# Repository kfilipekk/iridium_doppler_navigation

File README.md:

# NAVCORE-SoOP

A 46.5 × 47.2 mm, 6-layer STM32H743 flight controller that navigates without GPS using the Doppler shift of Iridium satellites. It runs ArduPilot with a MatekH743-compatible pinout. Made by Krystian Filipek for my GNSS-denied drone.

<div align="center">

</div>

## Results

### Castle Mound, Cambridge (16 Nov 2026)
First session under the real sky: the board on a tripod with the HC610 antenna, GPS denied in software for 30 and 52 minutes. In 1 h 42 min it heard 17,106 bursts and fused 11,383. Each S-curve is a satellite passing over: dots are measured bursts, lines are the Doppler predicted from its orbit.

Started 3 km off with no GPS and left at rest, Iridium alone settles to 50-130 m median error in replay.

### Two flights (18-19 Nov 2026)
On Stansted → Bremen and Hamburg → Gatwick the board was in my hand luggage at the window, logging the radio, IMU and cabin pressure, with a u-blox GPS logged as truth. I replayed the logs afterwards with GPS cut at wheels-off: the IMU corrected by Iridium Doppler, and the cabin barometer for height.

| Median error over 8 filter settings | Cruise (15-45 min) | Descent (45-75 min) |
|---|---|---|
| FR3634 Stansted → Bremen | 2.8-3.0 km | 3.7-6.0 km |
| EZY8636 Hamburg → Gatwick | 3.5-3.9 km | 3.2-3.4 km |
| The same IMU without Iridium | over 1,000 km | |

None of the 16 runs diverged. The orbits are Space-Track elements from before take-off.

<div align="center">

</div>

These are replays of the logs. In the air the I/Q was mirrored (see Known Issues), so nothing decoded live. The firmware fixes that now; a live run is next.

## Features

### Iridium Navigation
Optical flow and visual-inertial odometry drift without bound over long flights. Iridium NEXT satellites orbit at ~780 km and ~7.5 km/s, and their Ring Alert bursts at 1626.27 MHz arrive shifted by up to ±36 kHz. The shift depends on where you are, so enough bursts give a position, and unlike the IMU it doesn't drift.

- **L-band Receiver** - MAX2112 direct-conversion tuner and OPA2374 baseband filter into the ADCs
- **Antenna Feed** - MMCX port with a current-limited 5 V feed for the active antenna, reported as open, ok or short
- **On-board Navigation** - burst detection, SGP4 orbits and the position solve run on the H743 and feed ArduPilot's EKF as a GPS
- **Spoofing Check** - the real GPS is checked against the Iridium-only fix before it is trusted

### Hardware
| Subsystem | Components |
|-----------|------------|
| MCU | STM32H743VIT6, Cortex-M7 @ 480 MHz, 2 MB flash, 1 MB RAM |
| IMUs | ICM-45686 (SPI1) and ICM-42605 (SPI4) on a separate analogue 3.3 V rail, shared with the tuner |
| Barometer | MS5611 on I2C2 |
| Storage | W25Q128 flash for the orbit catalogue, microSD over SDIO |
| Power | 3S-5S input with TVS and reverse-polarity protection, two LMR33630 bucks (1.6 A system, 2.1 A payload) and three 3.3 V LDOs |
| Connectors | Latching JST-GH on every cable port, two servo headers, MMCX, USB-C, TC2030 SWD pads |
| Protection | ESD clamp on every cable-facing signal, series resistors on the motor, telemetry, current, lidar and servo lines |

### Layer Stackup
```
F.Cu:   MCU, RF receiver, bucks and LDOs, flash, the edge connectors
In1.Cu: Continuous ground plane
In2.Cu: Mixed signal with GND fill
In3.Cu: Mixed signal with GND fill
In4.Cu: Split power planes (+5V, +5V_PAYLOAD, +3V3, VBAT)
B.Cu:   IMUs, baro, both crystals, CAN, microSD, the underside connectors
```

### On the Drone
30.5 mm stack mount, DShot ESC on `J2`, optical flow on `J14`, lidar on `J11`, companion computer on `J21`, DroneCAN on `J6`

### How It Compares
| | NAVCORE-SoOP | SpeedyBee F405 V4 | Matek H743-SLIM V3 | Pixhawk 6C |
|---|---|---|---|---|
| MCU | STM32H743 | STM32F405 | STM32H743 | STM32H743 + F103 |
| IMUs | ICM-45686 + ICM-42605 | ICM-42688-P | ICM-42688-P + ICM-42605 | ICM-42688-P + BMI088 |
| Input | 3-5S | 3-6S | 2-8S | power module |
| Port ESD | every cable signal | none stated | none stated | none stated |
| Position without GNSS | Iridium Doppler | none | none | none |

It has no OSD and no 9-12 V video rail, and it takes 5S at most.

## Known Issues (Rev E)

- **I/Q mirrored.** The I and Q channels arrive swapped, so the receiver heard every burst's mirror image, about 25 dB down. The firmware now turns the spectrum the right way up from Ring Alert decodes (`swap_iq` in `soop.cfg` forces it).
- **RF line impedance.** The board was ordered on JLCPCB's default stackup, which puts the antenna line near 67 Ω rather than 50 Ω.
- **No PPS line.** ArduPilot stamps u-blox fixes when the message arrives, so `gps_lag_s` corrects the time tag. An optional PPS input on TP3 is wired in firmware but untested.
- **Channel 4 unused.** The channel at 1626.4375 MHz carries about 55% more bursts but sits outside the DSP's ±62.5 kHz window; using it live needs a second window.

## Getting Started

### Prerequisites
- **KiCad 9** to open the board and schematic
- **Python 3** with numpy and sgp4, and **ngspice** for the circuit simulations
- **ArduPilot toolchain** for the firmware (`tools/build_firmware.sh` pins Copter-4.7.0)

### Building
1. Clone the repository:
   ```bash
   git clone https://github.com/kfilipekk/iridium_drone.git
   cd iridium_drone
   ```

2. Simulate the analogue blocks (bucks, LDOs, antenna feed, tuner PLL, baseband filter):
   ```bash
   python3 sim/run_suite.py
   ```

3. Build the navigation code and its tests for the host (SGP4, burst detection, the position solve):
   ```bash
   make -C firmware/soop
   ```

4. Build ArduPilot for the board with the SoOP backend:
   ```bash
   bash tools/build_firmware.sh
   ```

### Checking the Board
The checks need KiCad's Python (the `pcbnew` module), and `irdrop.py` needs numpy. Run them from the repository root:
```bash
kicad-cli pcb drc --schematic-parity NAVCORE-SoOP.kicad_pcb
python3 tools/check.py geometry     # acute corners, dangling ends, dead copper, vias in pads
python3 tools/check.py backside     # pins landing under parts on the other side
python3 tools/check.py footprints   # pad counts against JLCPCB's own parts
python3 tools/irdrop.py check       # DC drop and current density on every power rail
python3 tools/fab.py bundle         # gerbers, BOM, CPL and the order sheet, into fab/
```
`--help` on any of them lists the rest.

### Field Sessions and Replays
```bash
python3 tools/soop_plan.py 52.212 0.115           # rank the next hours by satellite geometry
python3 tools/soop_session.py OUT.csv off:1800,on:300   # record both receivers, deny GPS on a plan
python3 tools/soop_live.py OUT.csv                # watch it in the browser
python3 tools/soop_replay.py LOG.BIN TLE --static # run a log through the navigation again
python3 tools/soop_extract.py LOG.BIN LOG.npz     # a flight log to numpy
python3 tools/soop_ins.py LOG.npz TLE BURSTS.csv TRUTH.npz --out FIXES.csv
python3 tools/soop_flightmap.py --flight "LABEL|LOG.npz|FIXES.csv" --basemap DIR map.html
```

### Ordering
The JLCPCB files are in `fab/`: the Gerber and drill bundle, BOM, pick-and-place and schematic PDF. Order 6 layers, 1 oz copper inside and out, ENIG, epoxy-filled and capped vias, and assembly on both sides. Name a controlled-impedance stackup if you want the antenna line at 50 Ω.

## Repository Structure

```
├── NAVCORE-SoOP.kicad_pcb   # PCB
├── NAVCORE-SoOP.kicad_sch   # Schematic, generated from tools/design.py
├── fab/                     # JLCPCB order files
├── firmware/                # ArduPilot hwdef, the SoOP backend and the on-board navigation
├── tools/                   # Design model, board checks, and the soop_* field and replay tools
├── sim/                     # ngspice simulations of the analogue blocks
├── sitl/tle/                # Iridium orbital elements for the host tools
├── cad/                     # OpenSCAD airframe, printed mounts and renders
└── libraries/               # Footprint and symbol libraries
```

## Next

- A live run on the current firmware at Castle Mound
- A second DSP window so channel 4 is used live
- Per-satellite transmitter offsets and fresher orbits, which set the static floor more than the DSP does
- A downward radar for velocity, then flying it on the drone
- Writing up the airliner results

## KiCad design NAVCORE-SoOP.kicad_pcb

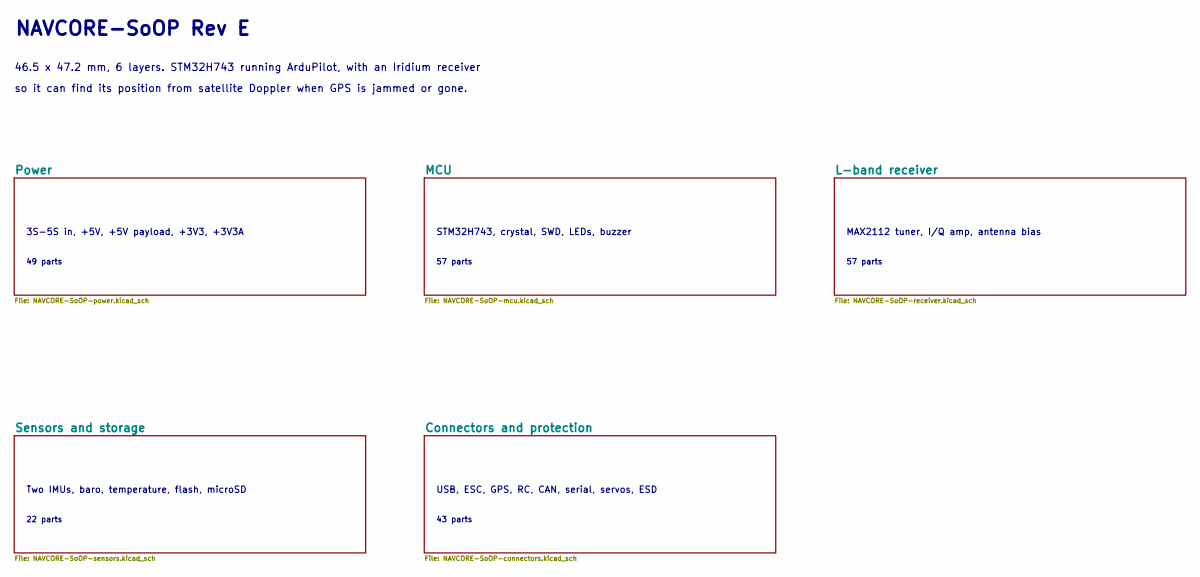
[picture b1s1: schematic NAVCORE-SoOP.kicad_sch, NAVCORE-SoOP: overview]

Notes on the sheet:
NAVCORE-SoOP Rev E
46.5 x 47.2 mm, 6 layers. STM32H743 running ArduPilot, with an Iridium receiver
so it can find its position from satellite Doppler when GPS is jammed or gone.
3S-5S in, +5V, +5V payload, +3V3, +3V3A
49 parts
STM32H743, crystal, SWD, LEDs, buzzer
57 parts
MAX2112 tuner, I/Q amp, antenna bias
Two IMUs, baro, temperature, flash, microSD
22 parts
USB, ESC, GPS, RC, CAN, serial, servos, ESD
43 parts

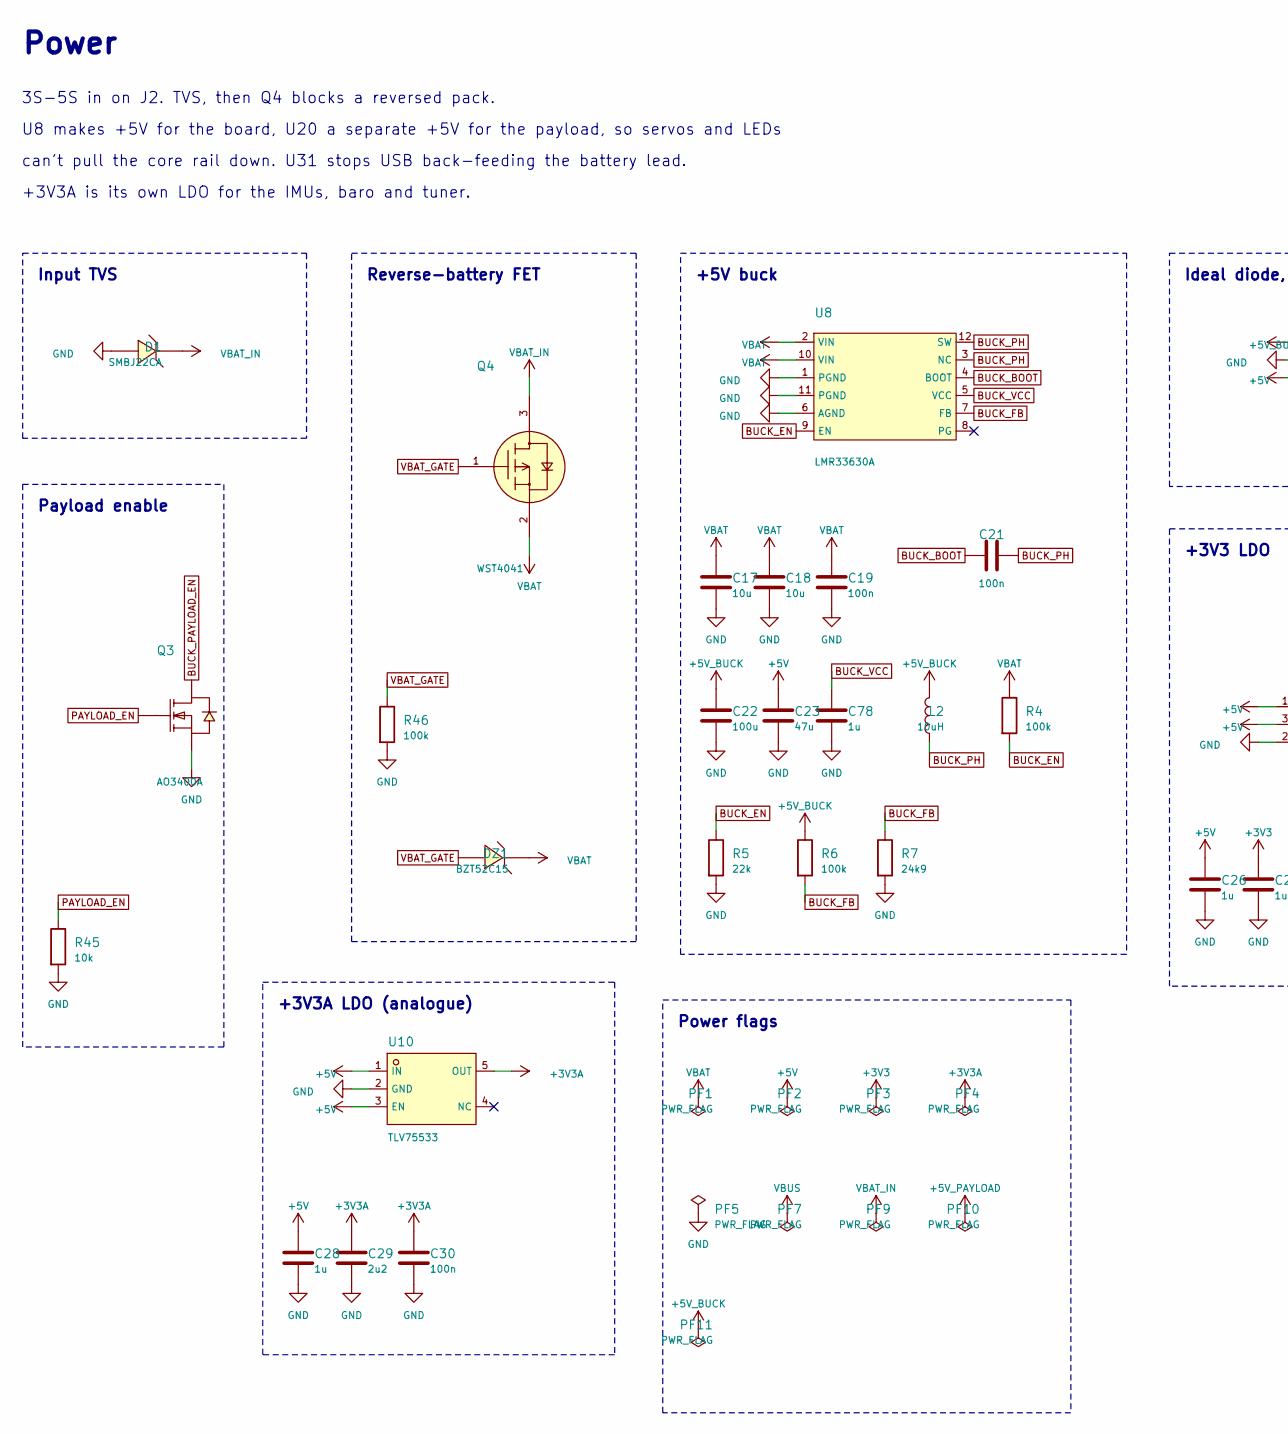
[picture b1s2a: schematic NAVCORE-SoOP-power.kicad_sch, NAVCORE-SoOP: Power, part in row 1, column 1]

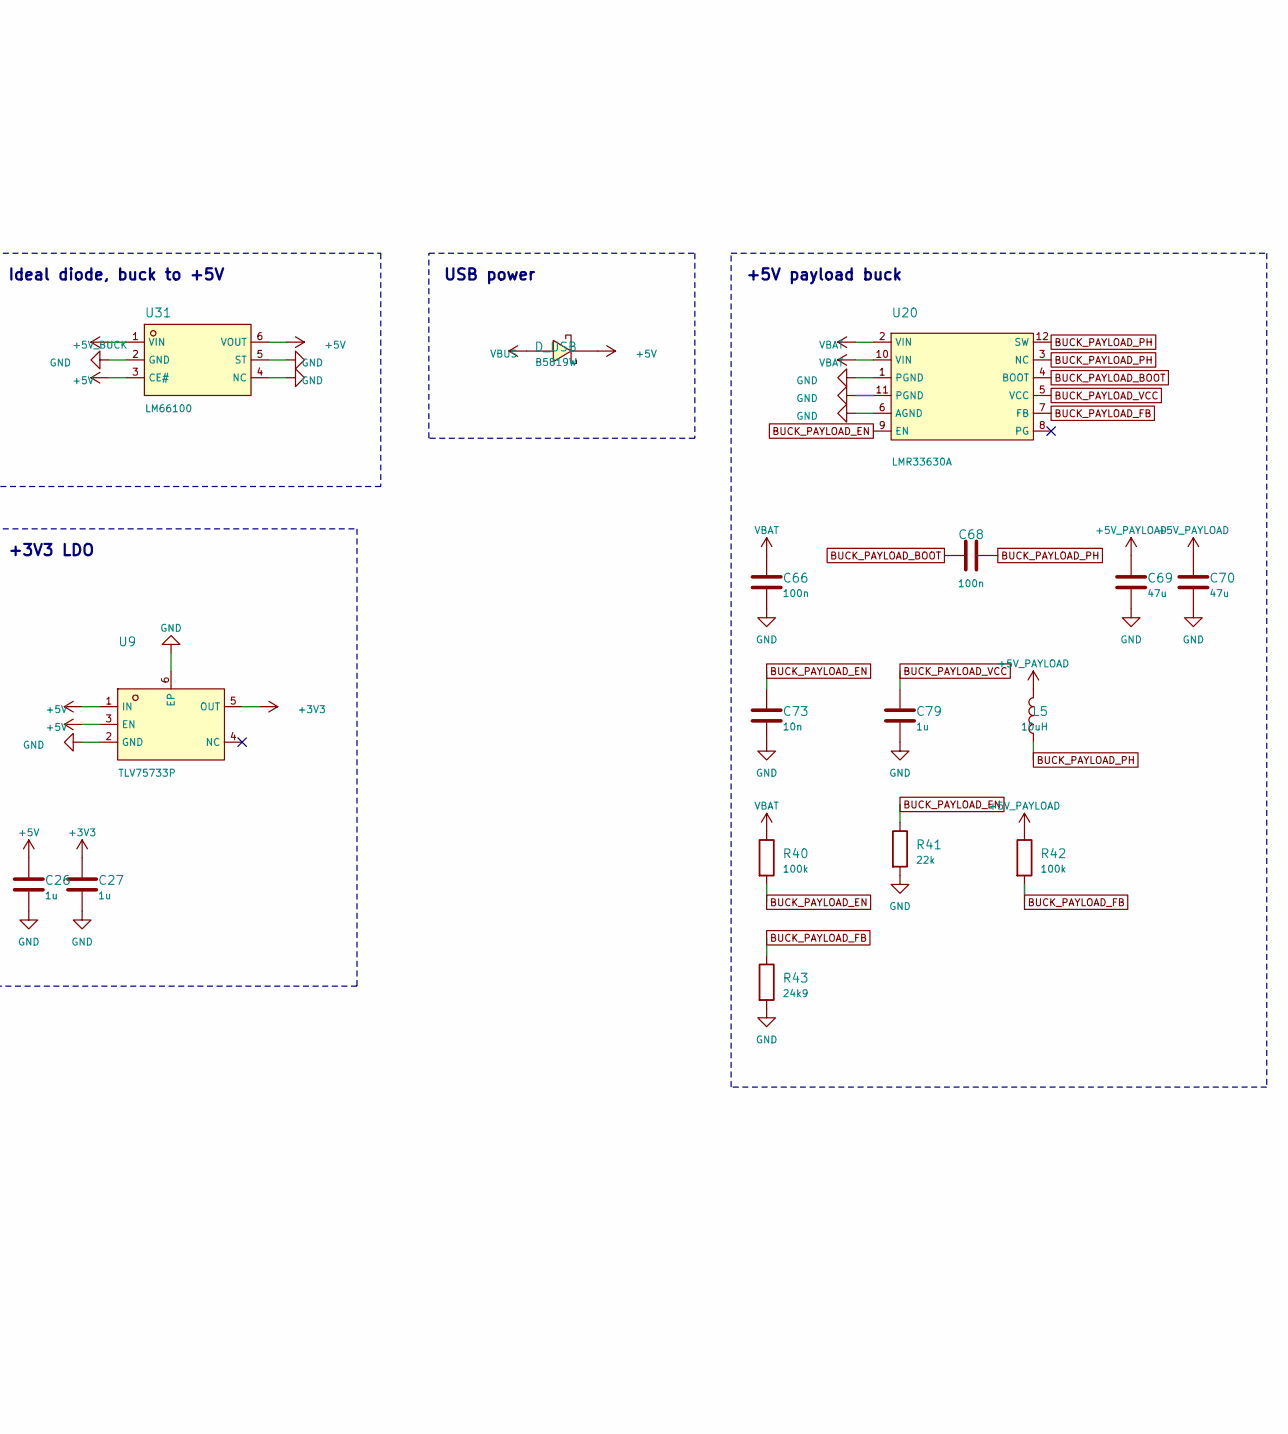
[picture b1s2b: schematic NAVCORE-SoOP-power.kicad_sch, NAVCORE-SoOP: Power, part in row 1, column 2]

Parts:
C17, C18: 10u; C_1206_3216Metric; LCSC C13585
C19, C66: 100n; C_0402_1005Metric; LCSC C307331
C21, C30, C68: 100n; C_0402_1005Metric; LCSC C1525
C22: 100u; C_1206_3216Metric; LCSC C883598
C23, C69, C70: 47u; C_1206_3216Metric; LCSC C96123
C26, C27, C28, C78, C79: 1u; C_0402_1005Metric; LCSC C52923
C29: 2u2; C_0402_1005Metric; LCSC C12530
C73: 10n; C_0402_1005Metric; LCSC C15195
D1: SMBJ22CA; SMB_L4.6-W3.6-LS5.3-RD; LCSC C113994
DZ1: BZT52C15; SOD-123_L2.7-W1.6-LS3.7-RD; LCSC C173427
D_USB: B5819W; SOD-123_L2.7-W1.6-LS3.7-RD-1; LCSC C8598
L2: 10uH; L_APV_ANR4030; LCSC C167879
L5: 10uH; L_APV_ANR5040; LCSC C354610
PF1, PF2, PF3, PF4, PF5, PF7, PF9, PF10, PF11: PWR_FLAG
Q3: AO3400A; SOT-23-3_L2.9-W1.3-P1.90-LS2.4-BR; LCSC C20917
Q4: WST4041; SOT-23-3_L2.9-W1.3-P1.90-LS2.4-BR; LCSC C148357
R4, R6, R40, R42, R46: 100k; R_0402_1005Metric; LCSC C25741
R5, R41: 22k; R_0402_1005Metric; LCSC C25768
R7, R43: 24k9; R_0402_1005Metric; LCSC C25874
R45: 10k; R_0402_1005Metric; LCSC C25744
U8, U20: LMR33630A; VQFN-12_L3.0-W2.0-P0.65-BL_TI_RNX; LCSC C2861505
U9: TLV75733P; SOT-23-5_L2.9-W1.6-P0.95-LS2.8-BL-EP; LCSC C22399950
U10: TLV75533; SOT-23-5_L3.0-W1.7-P0.95-LS2.8-BR; LCSC C404027
U31: LM66100; SC-70-6_L2.0-W1.3-P0.65-LS2.1-BL; LCSC C2869734

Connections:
+3V3: C27.1, PF3.1, U9.5 (OUT); also elsewhere on the board
+3V3A: C29.1, C30.1, PF4.1, U10.5 (OUT); also elsewhere on the board
+5V: C23.1, C26.1, C28.1, D_USB.1 (-), PF2.1, U9.1 (IN), U9.3 (EN), U10.1 (IN), U10.3 (EN), U31.3 (CE#), U31.6 (VOUT); also elsewhere on the board
+5V_BUCK: C22.1, L2.2, PF11.1, R6.1, U31.1 (VIN)
+5V_PAYLOAD: C69.1, C70.1, L5.2, PF10.1, R42.1; also elsewhere on the board
BUCK_BOOT: C21.1, U8.4 (BOOT)
BUCK_EN: R4.2, R5.1, U8.9 (EN)
BUCK_FB: R6.2, R7.1, U8.7 (FB)
BUCK_PAYLOAD_BOOT: C68.1, U20.4 (BOOT)
BUCK_PAYLOAD_EN: C73.1, Q3.3 (D), R40.2, R41.1, U20.9 (EN)
BUCK_PAYLOAD_FB: R42.2, R43.1, U20.7 (FB)
BUCK_PAYLOAD_PH: C68.2, L5.1, U20.3 (NC), U20.12 (SW)
BUCK_PAYLOAD_VCC: C79.1, U20.5 (VCC)
BUCK_PH: C21.2, L2.1, U8.3 (NC), U8.12 (SW)
BUCK_VCC: C78.1, U8.5 (VCC)
GND: C17.2, C18.2, C19.2, C22.2, C23.2, C26.2, C27.2, C28.2, C29.2, C30.2, C66.2, C69.2, C70.2, C73.2, C78.2, C79.2, D1.2 (A2), PF5.1, Q3.2 (S), R5.2, R7.2, R41.2, R43.2, R45.2, R46.2, U8.1 (PGND), U8.6 (AGND), U8.11 (PGND), U9.2 (GND), U9.6 (EP), U10.2 (GND), U20.1 (PGND), U20.6 (AGND), U20.11 (PGND), U31.2 (GND), U31.4 (NC), U31.5 (ST); also elsewhere on the board
PAYLOAD_EN: Q3.1 (G), R45.1; also elsewhere on the board
VBAT: C17.1, C18.1, C19.1, C66.1, DZ1.1 (K), PF1.1, Q4.2 (S), R4.1, R40.1, U8.2 (VIN), U8.10 (VIN), U20.2 (VIN), U20.10 (VIN); also elsewhere on the board
VBAT_GATE: DZ1.2 (A), Q4.1 (G), R46.1
VBAT_IN: D1.1 (A1), PF9.1, Q4.3 (D); also elsewhere on the board
VBUS: D_USB.2 (+), PF7.1; also elsewhere on the board

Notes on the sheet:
Power
3S-5S in on J2. TVS, then Q4 blocks a reversed pack.
U8 makes +5V for the board, U20 a separate +5V for the payload, so servos and LEDs
can't pull the core rail down. U31 stops USB back-feeding the battery lead.
+3V3A is its own LDO for the IMUs, baro and tuner.
Input TVS
Reverse-battery FET
+5V buck
Ideal diode, buck to +5V
USB power
+5V payload buck
Payload enable
+3V3 LDO
+3V3A LDO (analogue)
Power flags

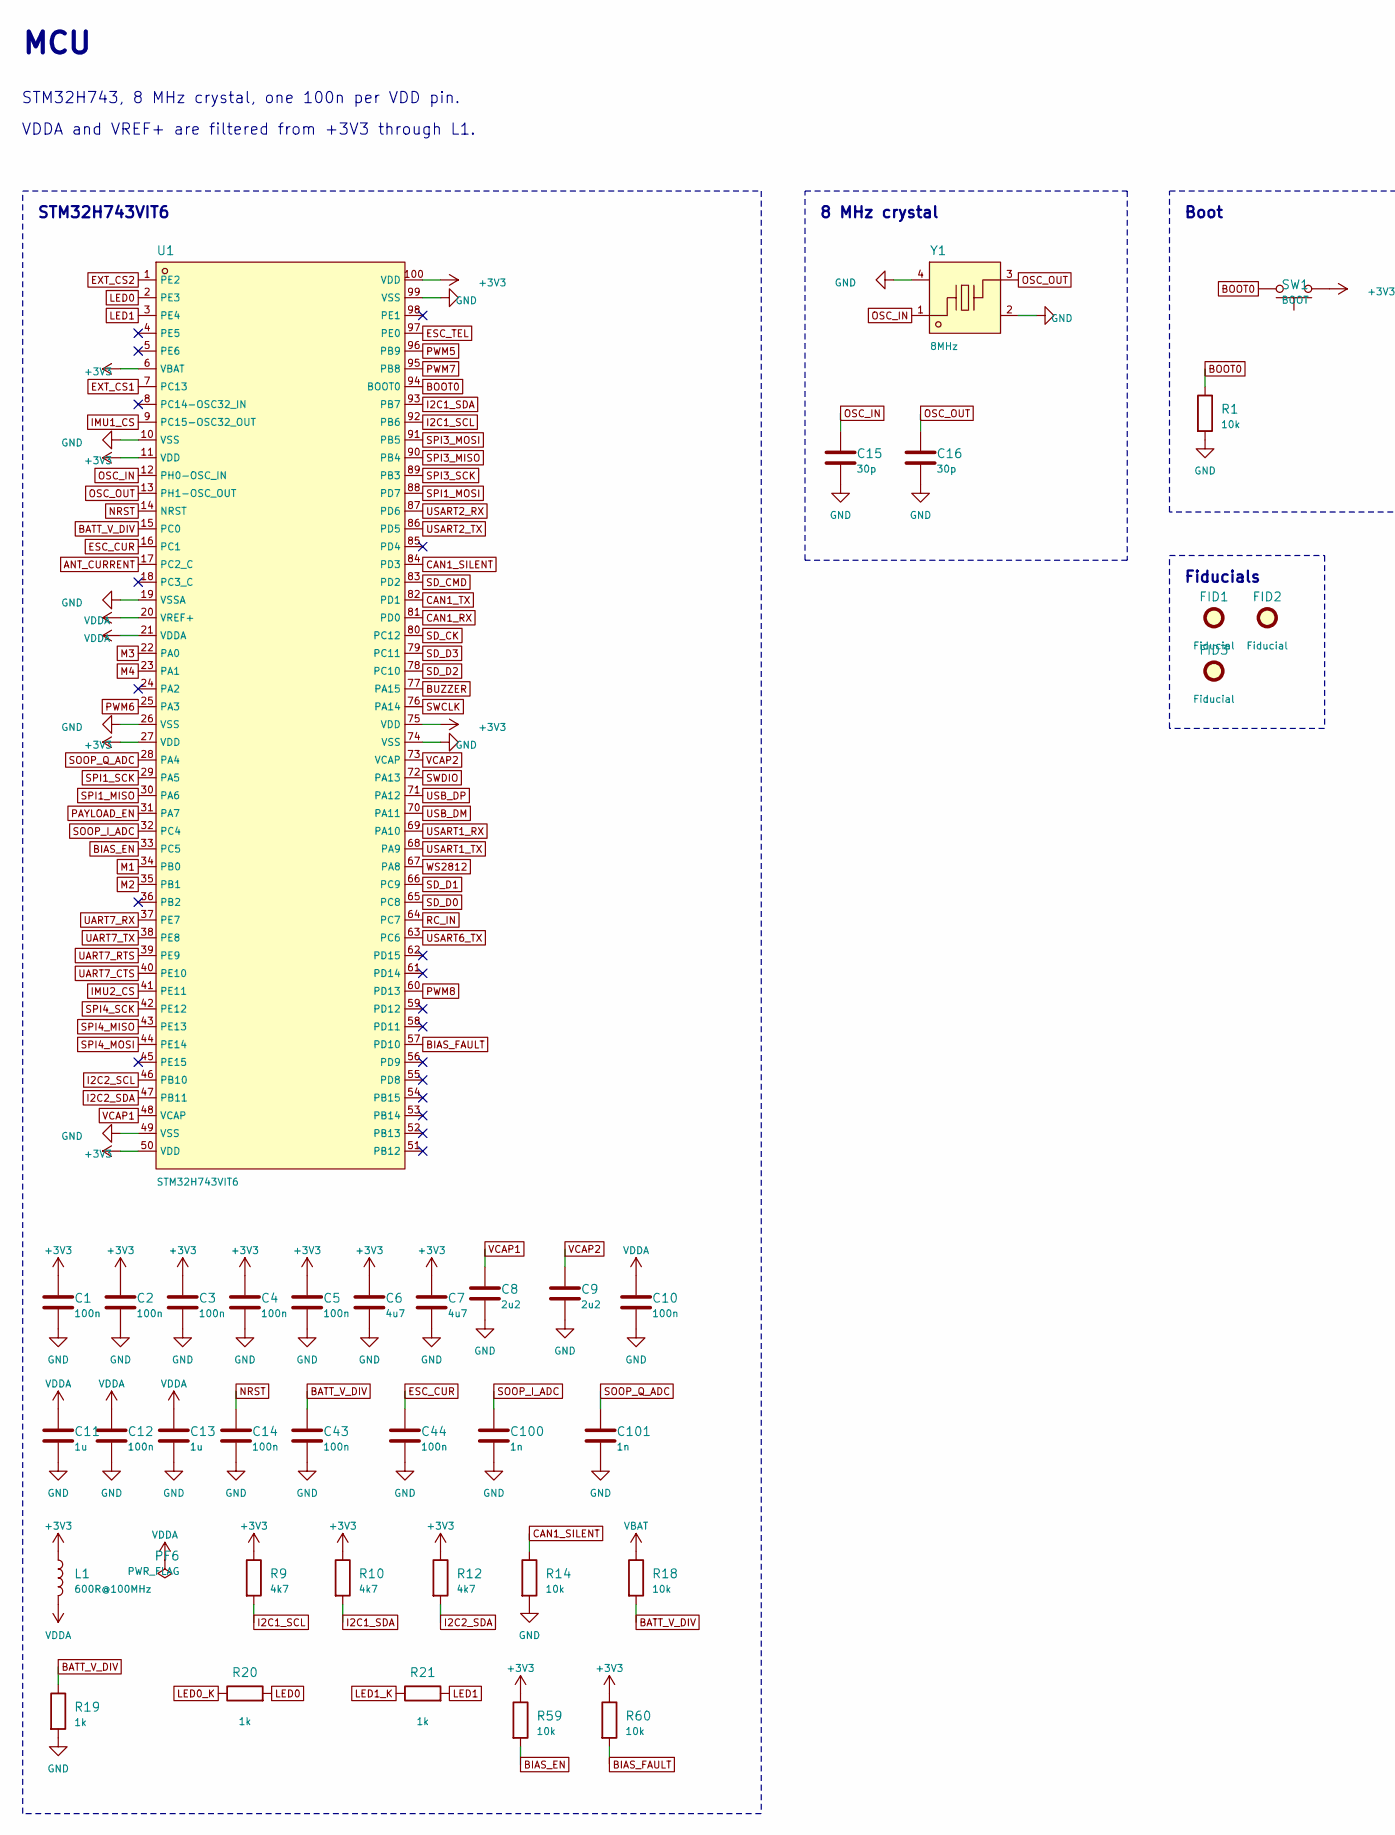
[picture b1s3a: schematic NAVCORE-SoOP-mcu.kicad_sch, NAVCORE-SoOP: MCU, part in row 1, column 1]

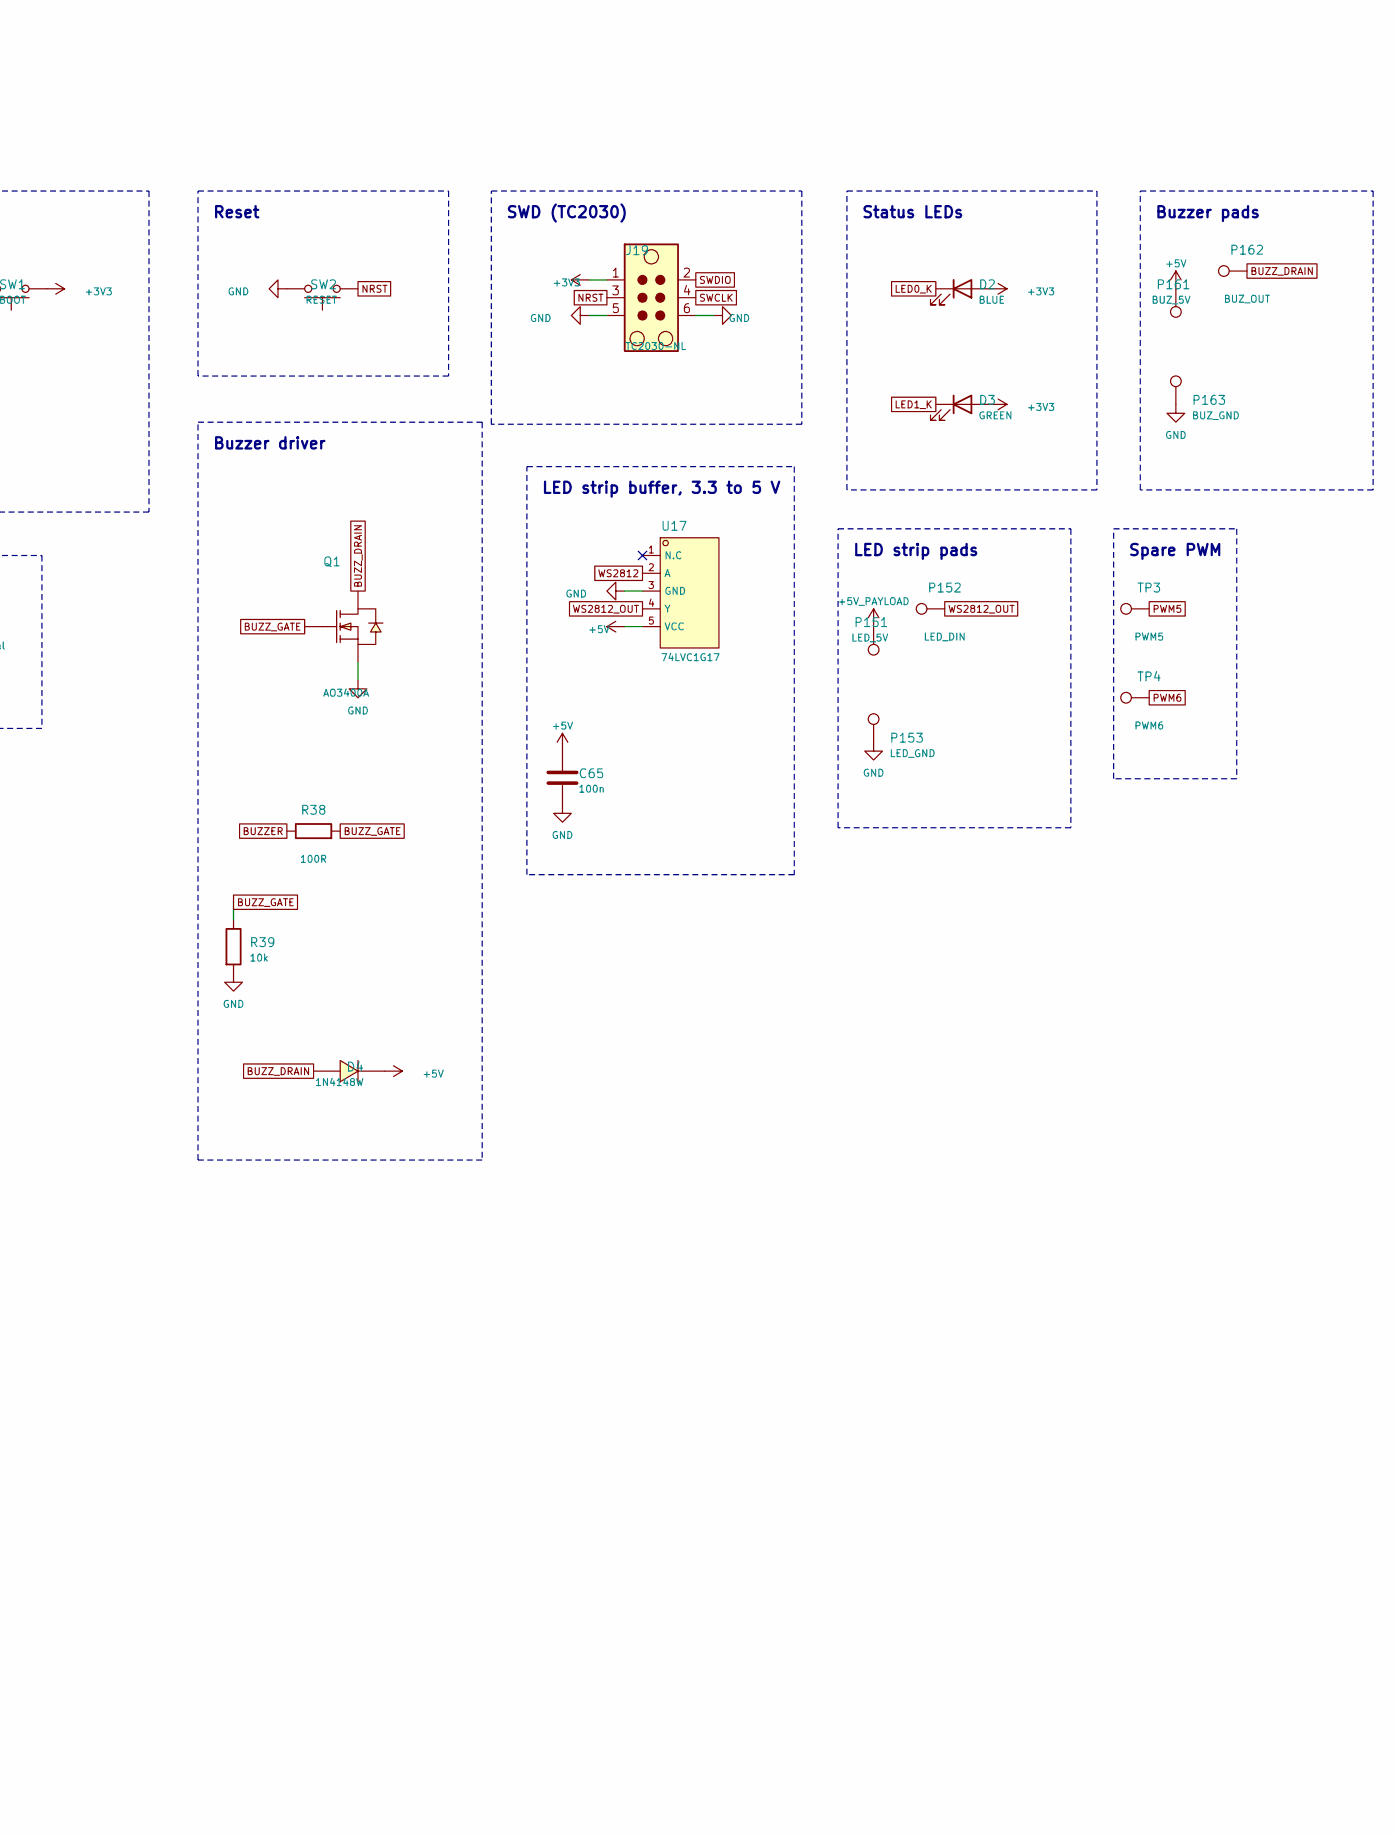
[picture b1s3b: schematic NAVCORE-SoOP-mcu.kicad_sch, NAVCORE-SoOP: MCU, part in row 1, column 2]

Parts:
C1, C2, C3, C4, C5, C10, C12, C14, C43, C44, C65: 100n; C_0402_1005Metric; LCSC C1525
C6, C7: 4u7; C_0805_2012Metric; LCSC C354262
C8, C9: 2u2; C_0402_1005Metric; LCSC C12530
C11, C13: 1u; C_0402_1005Metric; LCSC C52923
C15, C16: 30p; C_0402_1005Metric; LCSC C107004
C100, C101: 1n; C_0201_0603Metric; LCSC C710792
D2: BLUE; LED_0603_1608Metric; LCSC C965807
D3: GREEN; LED_0603_1608Metric; LCSC C965804
D4: 1N4148W; SOD-123F_L2.7-W1.6-LS3.8-RD; LCSC C81598
FID1, FID2, FID3: Fiducial; Fiducial_1mm_Mask2mm
J19: TC2030-NL; Tag-Connect_TC2030-IDC-NL_2x03_P1.27mm_Vertical
L1: 600R@100MHz; L_0805_2012Metric; LCSC C1017
P151: LED_5V; TestPoint_Pad_1.5x1.5mm
P152: LED_DIN; TestPoint_Pad_1.5x1.5mm
P153: LED_GND; TestPoint_Pad_1.5x1.5mm
P161: BUZ_5V; TestPoint_Pad_1.5x1.5mm
P162: BUZ_OUT; TestPoint_Pad_1.5x1.5mm
P163: BUZ_GND; TestPoint_Pad_1.5x1.5mm
PF6: PWR_FLAG
Q1: AO3400A; SOT-23-3_L2.9-W1.3-P1.90-LS2.4-BR; LCSC C20917
R1, R14, R39, R59, R60: 10k; R_0402_1005Metric; LCSC C25744
R9, R10, R12: 4k7; R_0402_1005Metric; LCSC C25900
R18: 10k; R_0603_1608Metric; LCSC C25804
R19, R20, R21: 1k; R_0402_1005Metric; LCSC C11702
R38: 100R; R_0402_1005Metric; LCSC C25076
SW1: BOOT; SW_SPST_B3U-1000P; LCSC C231329
SW2: RESET; SW_SPST_B3U-1000P; LCSC C231329
TP3: PWM5; TestPoint_Pad_1.5x1.5mm
TP4: PWM6; TestPoint_Pad_1.5x1.5mm
U1: STM32H743VIT6; LQFP-100_L14.0-W14.0-P0.50-LS16.0-BL; LCSC C5271084
U17: 74LVC1G17; SOT-23-5_L3.0-W1.7-P0.95-LS2.8-BR; LCSC C7836
Y1: 8MHz; CRYSTAL-SMD_4P-L3.2-W2.5-BL; LCSC C2682774

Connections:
+3V3: C1.1, C2.1, C3.1, C4.1, C5.1, C6.1, C7.1, D2.2 (A), D3.2 (A), J19.1, L1.1, R9.1, R10.1, R12.1, R59.1, R60.1, SW1.1, U1.6 (VBAT), U1.11 (VDD), U1.27 (VDD), U1.50 (VDD), U1.75 (VDD), U1.100 (VDD); also elsewhere on the board
+5V: C65.1, D4.1 (K), P161.1, U17.5 (VCC); also elsewhere on the board
+5V_PAYLOAD: P151.1; also elsewhere on the board
ANT_CURRENT: U1.17 (PC2_C); also elsewhere on the board
BATT_V_DIV: C43.1, R18.2, R19.1, U1.15 (PC0)
BIAS_EN: R59.2, U1.33 (PC5); also elsewhere on the board
BIAS_FAULT: R60.2, U1.57 (PD10); also elsewhere on the board
BOOT0: R1.1, SW1.2, U1.94 (BOOT0)
BUZZER: R38.1, U1.77 (PA15)
BUZZ_DRAIN: D4.2 (A), P162.1, Q1.3 (D)
BUZZ_GATE: Q1.1 (G), R38.2, R39.1
CAN1_RX: U1.81 (PD0); also elsewhere on the board
CAN1_SILENT: R14.1, U1.84 (PD3); also elsewhere on the board
CAN1_TX: U1.82 (PD1); also elsewhere on the board
ESC_CUR: C44.1, U1.16 (PC1); also elsewhere on the board
ESC_TEL: U1.97 (PE0); also elsewhere on the board
EXT_CS1: U1.7 (PC13); also elsewhere on the board
EXT_CS2: U1.1 (PE2); also elsewhere on the board
GND: C1.2, C2.2, C3.2, C4.2, C5.2, C6.2, C7.2, C8.2, C9.2, C10.2, C11.2, C12.2, C13.2, C14.2, C15.2, C16.2, C43.2, C44.2, C65.2, C100.2, C101.2, J19.5, J19.6, P153.1, P163.1, Q1.2 (S), R1.2, R14.2, R19.2, R39.2, SW2.2, U1.10 (VSS), U1.19 (VSSA), U1.26 (VSS), U1.49 (VSS), U1.74 (VSS), U1.99 (VSS), U17.3 (GND), Y1.2 (GND), Y1.4 (GND); also elsewhere on the board
I2C1_SCL: R9.2, U1.92 (PB6); also elsewhere on the board
I2C1_SDA: R10.2, U1.93 (PB7); also elsewhere on the board
I2C2_SCL: U1.46 (PB10); also elsewhere on the board
I2C2_SDA: R12.2, U1.47 (PB11); also elsewhere on the board
IMU1_CS: U1.9 (PC15-OSC32_OUT); also elsewhere on the board
IMU2_CS: U1.41 (PE11); also elsewhere on the board
LED0: R20.2, U1.2 (PE3)
LED0_K: D2.1 (K), R20.1
LED1: R21.2, U1.3 (PE4)
LED1_K: D3.1 (K), R21.1
M1: U1.34 (PB0); also elsewhere on the board
M2: U1.35 (PB1); also elsewhere on the board
M3: U1.22 (PA0); also elsewhere on the board
M4: U1.23 (PA1); also elsewhere on the board
NRST: C14.1, J19.3, SW2.1, U1.14 (NRST)
OSC_IN: C15.1, U1.12 (PH0-OSC_IN), Y1.1
OSC_OUT: C16.1, U1.13 (PH1-OSC_OUT), Y1.3
PAYLOAD_EN: U1.31 (PA7); also elsewhere on the board
PWM5: TP3.1, U1.96 (PB9)
PWM6: TP4.1, U1.25 (PA3)
PWM7: U1.95 (PB8); also elsewhere on the board
PWM8: U1.60 (PD13); also elsewhere on the board
RC_IN: U1.64 (PC7); also elsewhere on the board
SD_CK: U1.80 (PC12); also elsewhere on the board
SD_CMD: U1.83 (PD2); also elsewhere on the board
SD_D0: U1.65 (PC8); also elsewhere on the board
SD_D1: U1.66 (PC9); also elsewhere on the board
SD_D2: U1.78 (PC10); also elsewhere on the board
SD_D3: U1.79 (PC11); also elsewhere on the board
SOOP_I_ADC: C100.1, U1.32 (PC4); also elsewhere on the board
SOOP_Q_ADC: C101.1, U1.28 (PA4); also elsewhere on the board
SPI1_MISO: U1.30 (PA6); also elsewhere on the board
SPI1_MOSI: U1.88 (PD7); also elsewhere on the board
SPI1_SCK: U1.29 (PA5); also elsewhere on the board
SPI3_MISO: U1.90 (PB4); also elsewhere on the board
SPI3_MOSI: U1.91 (PB5); also elsewhere on the board
SPI3_SCK: U1.89 (PB3); also elsewhere on the board
SPI4_MISO: U1.43 (PE13); also elsewhere on the board
SPI4_MOSI: U1.44 (PE14); also elsewhere on the board
SPI4_SCK: U1.42 (PE12); also elsewhere on the board
SWCLK: J19.4, U1.76 (PA14)
SWDIO: J19.2, U1.72 (PA13)
UART7_CTS: U1.40 (PE10); also elsewhere on the board
UART7_RTS: U1.39 (PE9); also elsewhere on the board
UART7_RX: U1.37 (PE7); also elsewhere on the board
UART7_TX: U1.38 (PE8); also elsewhere on the board
USART1_RX: U1.69 (PA10); also elsewhere on the board
USART1_TX: U1.68 (PA9); also elsewhere on the board
USART2_RX: U1.87 (PD6); also elsewhere on the board
USART2_TX: U1.86 (PD5); also elsewhere on the board
USART6_TX: U1.63 (PC6); also elsewhere on the board
USB_DM: U1.70 (PA11); also elsewhere on the board
USB_DP: U1.71 (PA12); also elsewhere on the board
VBAT: R18.1; also elsewhere on the board
VCAP1: C8.1, U1.48 (VCAP)
VCAP2: C9.1, U1.73 (VCAP)
VDDA: C10.1, C11.1, C12.1, C13.1, L1.2, PF6.1, U1.20 (VREF+), U1.21 (VDDA)
WS2812: U1.67 (PA8), U17.2 (A)
WS2812_OUT: P152.1, U17.4 (Y)

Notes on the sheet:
MCU
STM32H743, 8 MHz crystal, one 100n per VDD pin.
VDDA and VREF+ are filtered from +3V3 through L1.
STM32H743VIT6
8 MHz crystal
Boot
Reset
SWD (TC2030)
Status LEDs
Buzzer driver
Buzzer pads
LED strip buffer, 3.3 to 5 V
LED strip pads
Spare PWM
Fiducials

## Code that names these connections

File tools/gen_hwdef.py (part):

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    (r'^define OSD_ENABLED',     "no analogue OSD fitted"),
    (r'^define HAL_OSD_TYPE_DEFAULT', "no analogue OSD fitted"),
    (r'^ROMFS_WILDCARD libraries/AP_OSD', "no analogue OSD fitted"),
    (r'^PA4 BATT2_VOLTAGE_SENS', "single battery; freed for the SoOP I/Q input"),
    (r'^define HAL_BATT2_',      "single battery"),
    (r'^define HAL_DEFAULT_AIRSPEED_PIN', "no airspeed sensor"),
    (r'^define BOARD_RSSI_ANA_PIN', "RSSI arrives over CRSF"),
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    (r'^IMU Invensense SPI:mpu6000',  "MPU6000 not fitted"),
    (r'^SPIDEV icm20602',        "ICM-20602 not fitted"),
    (r'^SPIDEV mpu6000',         "MPU6000 not fitted"),
    (r'^PC7 TIM3_CH2 TIM3 RCININT',
     "RC is CRSF over USART6 (SERIAL7_PROTOCOL 23), so the timer input on the same pin goes, "
     "and TIM3 drives M1/M2 instead (PPM/SBUS-by-timer receivers lose their input)"),
    (r'^PB13 SPI2_SCK',          "SPI2 served only the analogue OSD, which is not fitted"),
    (r'^PB14 SPI2_MISO',         "SPI2 served only the analogue OSD, which is not fitted"),
    (r'^PB15 SPI2_MOSI',         "SPI2 served only the analogue OSD, which is not fitted"),
    (r'^PC13 IMU3_CS',           "no third IMU fitted; PC13 is the flow port's chip select"),
    (r'^PB9 UART4_TX',           "UART4 was never brought out; PB8 now carries servo PWM7"),
    (r'^PB8 UART4_RX',           "UART4 was never brought out; PB8 now carries servo PWM7"),
    (r'^PD14 TIM4_CH3',          "PWM9 had no connector; TIM4_CH3 is PWM7's on PB8"),
    (r'^PD15 TIM4_CH4',          "PWM10 had no connector; TIM4_CH4 is PWM5's on PB9"),
    (r'^PE1 UART8_TX',
     "ESC telemetry is receive-only, so UART8 needs only PE0/RX. PE1 is left "
     "unwired rather than declared and unconnected"),
]

#lines to rewrite: pins MatekH743 uses for something else
REPLACE = [
    (r'^PA7 BATT2_CURRENT_SENS',
     "PA7 PAYLOAD_EN OUTPUT LOW GPIO(83)",
     "MatekH743 reads PA7 as BATT2_CURRENT_SENS. This board has one battery, so the pin "
     "was free, and it now drives Q3's gate to switch the 5 V Payload rail (U20). LOW leaves "
     "the rail enabled - R45 pulls the gate down as well - so payload fails safe towards "
     "powered. It is deliberately a pin MatekH743 only ever READS: a stock MatekH743 "
     "binary cannot assert it and so cannot cut payload power."),
    (r'^PC4 PRESSURE_SENS ADC1 SCALE\(2\)',
     "PC4 SOOP_I_ADC ADC1 SCALE(1)",
     "No airspeed sensor: PC4 is the tuner's I, through the OPA2374 stage. Declared on ADC1 so "
     "the DMA resolver gives ADC1/ADC2 a stream of their own; AnalogIn leaves ADC1 alone "
     "(tools/install_soop_backend.py) and AP_SoOP_Capture samples it with Q on ADC2."),
    (r'^PC0 BATT_VOLTAGE_SENS ADC1 SCALE\(1\)',
     "PC0 BATT_VOLTAGE_SENS ADC3 SCALE(1)",
     "Battery sensing moves to ADC3 (PC0 is ADC123_INP10, the same channel number), so "
     "ADC1 and ADC2 are free to sample the tuner's I and Q together - AP_SoOP_Capture."),
    (r'^PC1 BATT_CURRENT_SENS ADC1 SCALE\(1\)',
     "PC1 BATT_CURRENT_SENS ADC3 SCALE(1)",
     "Battery current moves to ADC3 with the voltage (PC1 is ADC123_INP11)."),
    (r'^PC5 RSSI_ADC.*',
     "PC5 BIAS_EN OUTPUT HIGH GPIO(84)",
     "RSSI arrives over CRSF, so PC5 enables U24, the antenna's bias feed. HIGH, and R59 "
     "pulls it up, so the feed is on from power-up; AP_SoOP switches it off on a lasting "
     "short or when soop.cfg says ant_feed 0."),
    (r'^PD4 EXT_CS1 CS',
     "PC13 EXT_CS1 CS",
     "The flow port's chip select leaves PD4, on U1's north-west corner, for PC13 on the east "
     "side facing J14 and its clamp U29: the long run across the board would not route. "
     "PC13 is a low-drive RTC-domain pin (3 mA, 2 MHz), which a chip select that toggles once "
     "per transaction does not notice."),
    (r'^PD12 TIM4_CH1 TIM4 PWM\(7\) GPIO\(56\)',
     "PB8 TIM4_CH3 TIM4 PWM(7) GPIO(56)",
     "Servo 1 (J17) moves from PD12 on U1's west side to PB8 on the south edge, nearer J17: "
     "the run round U1 would not route. Same timer (TIM4) as PWM8, so the two servos keep "
     "one rate group."),
    (r'^PA2\s+TIM5_CH3\s+TIM5\s+PWM\(5\)\s+GPIO\(54\)',
     "PB9 TIM4_CH4 TIM4 PWM(5) GPIO(54)",
     "The spare servo output on test pad TP3 moves from PA2, whose escape faces the RF corner, "
     "to PB9 on U1's south edge beside TP3. It joins the servos' TIM4 rate group, and leaves "
     "TIM5 to the motors."),
    (r'^SERIAL_ORDER .*',
     "SERIAL_ORDER OTG1 UART7 USART1 USART2 USART3 UART8 EMPTY USART6",
     "Remove UART4 to free PB8 for PWM7 and drop nonexistent OTG2."),
    (r'^PD10\s+PINIO1.*',
     "PD10 BIAS_FAULT INPUT GPIO(85)",
     "U24's FAULT#, open drain, pulled up by R60: low on overcurrent, overtemperature or "
     "reverse voltage."),
    (r'^PD11\s+PINIO2.*',
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
#timers: same pins, other timers
REPLACE += [
    (r'^PB0\s+TIM8_CH2N.*', "PB0  TIM3_CH3 TIM3  PWM(1)  GPIO(50) BIDIR",
     "M1 moves from TIM8_CH2N (complementary - no input capture, so no BDShot) to TIM3_CH3 "
     "on the same pin, as MatekH743-bdshot does. BIDIR is set on the first channel of each "
     "pair, which reads for both."),
    (r'^PB1\s+TIM8_CH3N.*', "PB1  TIM3_CH4 TIM3  PWM(2)  GPIO(51)", "M2: TIM3_CH4, same pin."),
    (r'^PA0\s+TIM5_CH1.*', "PA0  TIM5_CH1  TIM5  PWM(3)  GPIO(52) BIDIR",
     "M3/M4 stay on TIM5 (MatekH743-bdshot moves them to TIM2, but TIM2_CH1 is the passive "
     "buzzer's tone on PA15)."),
    (r'^PC7 USART6_RX USART6 NODMA ALT\(1\)', "PC7 USART6_RX USART6 NODMA",
     "USART6_RX is PC7's only function now that the timer RC input is gone."),
    (r'^DMA_NOSHARE SPI1\* SPI4\*$', "DMA_NOSHARE SPI1* SPI4* TIM3* TIM5*",
     "the BDShot timers get DMA streams of their own, as the IMU buses do"),
]
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# useless. I2C1 is on the GPS connector - use the compass inside the GPS module.
define ALLOW_ARM_NO_COMPASS 1

# USB VBUS sensing is not wired to PA9 on this board (PA9 is USART1_TX on J11;
# VBUS feeds +5V_LOGIC through diode D_USB). Without this define, ChibiOS sets
# GCCFG_VBDEN and halts USB enumeration waiting for VBUS on PA9.
define BOARD_OTG_NOVBUSSENS 1

# U19, the TMP119 beside U9, needs this line or it is dead SILICON.
define AP_TEMPERATURE_SENSOR_ENABLED 1

# ADC1 samples the tuner's I (PC4, INP4) and ADC2 its Q (PA4, INP18) at the same instant, in
# dual regular-simultaneous mode, for the on-board Iridium navigation (AP_SoOP_Capture).
# Dual mode needs 32-bit ADC12 samples; the battery is on ADC3, above.
define STM32_ADC_DUAL_MODE TRUE
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    return f"""
# The antenna feed's current: U25 (INA180A2, x{a['gain']:.0f}) across R62 ({v} ohm), on PC2_C.
# PC2_C reaches ADC3_INP0 with its analogue switch open; AP_SoOP opens it (SYSCFG PMCR).
PC2 ANT_CURRENT ADC3 SCALE(1)
define HAL_SOOP_ANT_ADC_PIN 0
define HAL_SOOP_ANT_SENSE_OHM {ohm}f
define HAL_SOOP_ANT_GAIN {a['gain']:.1f}f
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                bl, flags=re.M)
    bl = bl.replace("# for Matek H743-WING bootloader",
                    "# for NAVCORE-SoOP bootloader")
    bl = bl.replace("PA12 OTG_FS_DP OTG1",
                    "PA12 OTG_FS_DP OTG1\ndefine BOARD_OTG_NOVBUSSENS 1")
    bl = bl.replace("# make sure Vsw is on during bootloader\nPD10  PINIO1 OUTPUT LOW\n\n", "")
    bl = bl.replace("PB12 MAX7456_CS CS\n", "")
    bl = bl.replace("PD4 EXT_CS1 CS\n", "")
    bl = bl.replace("PC13 IMU3_CS CS", "PC13 EXT_CS1 CS")
    bl = bl.replace("PE3 LED_BOOTLOADER OUTPUT LOW\ndefine HAL_LED_ON 0",
                    "PE3 LED_BOOTLOADER OUTPUT LOW\nPE4 LED_ACTIVITY OUTPUT HIGH\ndefine HAL_LED_ON 0")
    bl = re.split(r"# support flashing from SD card:", bl)[0].rstrip() + "\n"
    open(f"{OUT}/hwdef-bl.dat", "w").write(
        "# GENERATED by tools/gen_hwdef.py - do not hand-edit.\n" + bl)
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
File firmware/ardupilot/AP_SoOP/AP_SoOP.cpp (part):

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static const float MOVING_SPD = 3.0f;       //m/s: past this the u-blox has seen it move
static const double STILL_HOLD_S = 2.0;
static const uint32_t BARO_FRESH_MS = 30000;//time only: a cabin's baro, tied to the u-blox
static const uint8_t PPS_PIN = 54;           //TP3, PB9 (PWM5): SERVO5_FUNCTION -1
static const double PPS_HOLD_S = 1.5;        //a pairing serves until the next edge is due
static const uint32_t IQ_SYNC_BLOCKS = 1221; //~10 s of capture blocks between I/Q fsyncs
//a u-blox stamps a fix when its message arrives: the navigation measured 75 +- 3 ms against
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static const double GPS_LAG_S = 0.075;
static const uint32_t LEAP_S = 18;                                   //GPS - UTC since 2017
static const char *SOOP_DIR = "APM/SOOP";
//LED0 (blue, D2) and LED1 (green, D3) sink through PE3 and PE4: low is on
#if defined(HAL_GPIO_A_LED_PIN) && defined(HAL_GPIO_B_LED_PIN)
#define AP_SOOP_LEDS 1
static const uint8_t LED_BLUE = HAL_GPIO_B_LED_PIN, LED_GREEN = HAL_GPIO_A_LED_PIN;
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

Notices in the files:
README.md:
License: MIT
